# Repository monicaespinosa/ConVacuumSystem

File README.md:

# ConVacuumSystem
Later I will have time to explain what this is about. Let's start with the important things.

## Current circuit
The circuit (still to try) goes as following:

The setup still has to be simulated to find out V_c and to check the accuracy of the voltages selected for the grid and the plate.

## CST Simulations of the setup
The following setup was simulated:

Initially were the following voltages set:
* V_S 6.4 V
* V_C: 6.4 V
* V_G= 400 V
* V_P= 1000 V

The result for the obtained trajectory is shown below. The obtained current was around 5 mA.

However, the shape of the electron beams seems to change its shape in a very drastic way. Making the V_C smaller (more negative) should help concentring more the electrons to the center of the beam. A second simulation was made sweeping the voltage of the Wehnelt_Cylinider between -10 V and 6 V. 

As a result, the following charges on the plate were obtained:

Particles that come out of the coil:

They are only high when the voltage at the Wehnelt Cylinider is equal or higher than that of the coil. A new simulation sweeping Vc between 6.4V and 15.4V is been made. Results:

Evidently, the current (and as a consequence the particles getting to the plate) exists only when V_C>=V_S. The trajectories of the particles change however as they seem to be pushed into the cylinder (because of the higher voltage):

A new simulation setting the voltage on the grid V_G=800 V, putting a porcelain cylinder around the components (to simulate the glass cylinider) and moving the cylinider along the z-axis was made. The obtained trajectories are:

### Setting the voltage on the plate nearly to 0
Simulation with V_G = 1000 V and V_P = 4 V, and moving the cylinder to its initial position.

Simulation with the same parameters but moving the cylinder so its positioned closer to the plate.

Final simulation moving the cylinder back again and setting its voltage to -V_S.

### Variations of the voltage on the plate

Current incoming to the plate is the import_2 current.

Incoming particles:

### Changing the cathode
For all the following simulations the following voltages are set: V_S=6.4V, V_C=-30V V_G = 1000V and V_P = 4V.

#### Vertical filled PEC cylinder
Model:

Trajectories:

Total current leaving the cathode: 1.191e-03 mA

### Vertical hollow PEC cylinder
The cathode looks like the one before but is hollow with a thickness of 0.3 mm.

Trajectories:

Total current leaving the cathode: 9.14e-02 mA

### Toroid
Model:

Trajectories:

Total current leaving the cathode: 0.98 mA

### Rectangular cathode:
Model:

Trajectories: 

Total current leaving the cathode: 0.78 mA

### Sphere
Model:

Trajectories:

Total current leaving the cathode: 1.19 mA

### cut Cone:
Model:

It didn't emit any current when being put this way. However, when rotating like this:

The following trajectories are gotten:

Total current leaving the cathode: 0.71 mA

### Electron-gun Cathode
Model: 

It's a "cone" whose two planar circular faces are connected not by a rotated linear surface but a rotated exponential surface so it's internal radious get's thicker in an exponential way along the w axis as w decreases, simulating a pointy trunked cone. It was initially made small but only few particles were accelerated. Increasing its size and getting it closer to the grid produces the following trajectories:

The total current leaving the cathode was 9.35 mA. However the trajectories are messy and very disperse. After trying to move both the cathode and the grid further from the plate, because of the Wehnelt-Cylinder, the particles collide and then get dispersed again, without reaching the plate:

### Toroid-Coil

Model:

Trajectories: (actually a pretty straight beam)

However, the current incoming to the plate was not as high as expected. In this case, a variation of the voltage on the plate was made and the following curve obtained:

A dependency of the current to the voltage on the grid was also tested. The results below show in fact that the highest this voltage is, the highest the current.

As the shape of the beam seems to be well centered, another try using two toroids was given a shot. The model of the cathode goes as following:

As expected, the trajectories:

However the current across the platte is 50 uA. 

### Clapton Coil
This is the coil used normally for vapers. One of these was modelled in CST and looks like this:

The current incoming into the plate is 21.46uA. However, as the clapton coils that are found in the market have typically a diameter of 3.0mm, which for this project is too small. In order to increase the size of the cathode, a few of them can be placed together. For this purpose, four clapton coils forming a loop was simulated:

Trajectories: Not so straight directed to the center of the beam.

Current incoming to the plate: 0.18 mA

## Current measurement

### Methode
As mentioned before, this is the electrical structure of the setup:

The current measurement in between the plate and the voltage source V_p is more detailed here:

The current flowing through R_mess is theorically expected to be around 5mA according to the simulations. Supposing that the current is 10mA, the following circuit was simulated to choose the value of R_mess:

The voltage across Rm increases as Rm does. A value of Rm=140 ohm is temporarily chosen.

The following component is a amplifier that measures the voltage across the resistor R_mess and whose output is a digital signal whose amount of 1's is proportional to the current flowing through R_mess. The used amplifier is the Si8946A, that measures voltages between -62.5 mV and +62.5 mV, and whose output has a frequency of 10MHz. As this frequency is too high for a microcontroller like Arduino to read, a phase of signal conditioning is required. The simple RC filter produces an analog signal which corresponds to an average value of the quantity of 1's contained in the digital output of the amplifier. As this output is either a 0 or a 1, the analog response of the filter varies between 0V to 1V. However, as we intend to read this signal with Arduino, in order to take of advantage of all its measuring range the to-be-measured signal should be in the full range of 0V to 5V. This is the reason why an additional operational amplifier with a gain of 5 is used. The amplifier corresponds to the TLV9001 by Texas Instruments.

### PCB

The whole circuitry mentioned above, intended to be used for measuring the current caused by the electrons colliding into the plate and further flowing through R_mess, will be designed to be as close as posible to the plate. As not only the amount of current is important, but also the distribution of the electrons along the plate, this last is eventually going to be divided into many smaller plates whose incoming current will be measured separatedly. The first PCB designed to try the measuring circuitry has three plates. The PCB has two layers, one of them containing the plates

and the other one the Si8946A amplifiers and the connector in charge of providing feeding voltage and of letting the signals out. 

To know if the digital signal at 10 MHz is able to be carried by a normal jumper cable without using a SMA connector, some calculations need to be made:

Let's assume a square wave and use Bogatins rule of thumb [here](https://www.edn.com/rule-of-thumb-1-bandwidth-of-a-signal-from-its-rise-time/). According to the datasheet, the rise time is 20ns. The bandwidth of such a signal is 50 MHz, whose wavelength in free space is 6m, let's say 3m in the PCB. At 1/10th wavelength that's 30cm, which sets the upper limit to the jumper wire's length. 

Another option is to attach a second PCB using a PCB to PCB connector. 

>>>>>>> main

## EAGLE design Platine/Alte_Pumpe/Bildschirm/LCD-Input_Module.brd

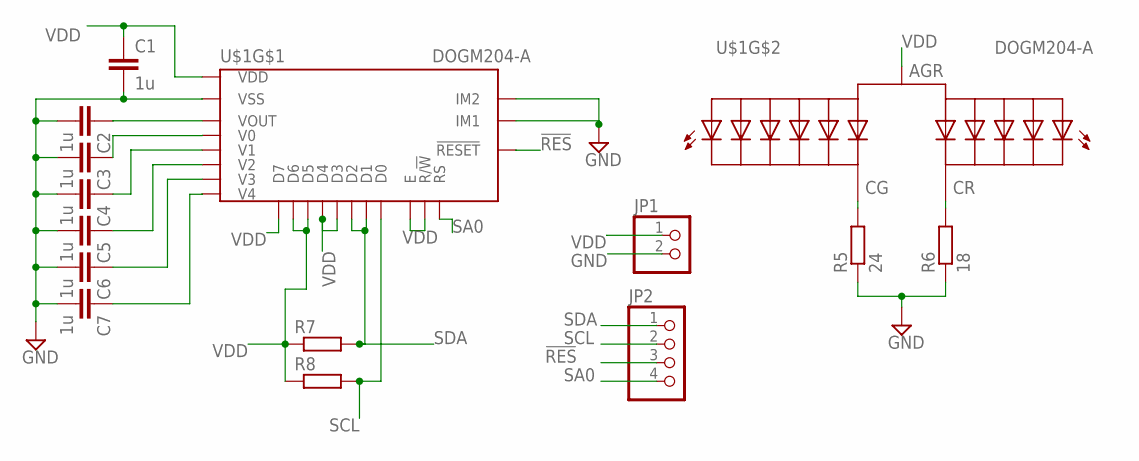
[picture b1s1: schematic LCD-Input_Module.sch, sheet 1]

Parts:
C1, C2, C3, C4, C5, C6, C7: 1u; C0603
JP1: PINHD-1X2; 1X02
JP2: PINHD-1X4; 1X04
R5: 24; R0603
R6: 18; R0603
R7, R8: R-EU_R0603; R0603
U$1: DOGM204-A; LCD

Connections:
!RES: JP2.3, U$1.P$44 (!RESET)
GND: C1.2, C2.2, C3.2, C4.2, C5.2, C6.2, C7.2, JP1.2, R5.1, R6.1, U$1.P$29 (IM2), U$1.P$30 (IM1), U$1.P$32 (VSS); also elsewhere on the board
unnamed: C3.1, U$1.P$24 (V0)
unnamed: C6.1, U$1.P$27 (V3)
unnamed: C4.1, U$1.P$25 (V1)
unnamed: C5.1, U$1.P$26 (V2)
unnamed: C7.1, U$1.P$28 (V4)
unnamed: C2.1, U$1.P$23 (VOUT)
unnamed: R5.2, U$1.P$21 (CG)
unnamed: R6.2, U$1.P$22 (CR)
SA0: JP2.4, U$1.P$43 (RS)
SCL: JP2.2, R8.2, U$1.P$40 (D0)
SDA: JP2.1, R7.2, U$1.P$38 (D2), U$1.P$39 (D1)
VDD: C1.1, JP1.1, R7.1, R8.1, U$1.P$1 (AGR), U$1.P$31 (VDD), U$1.P$33 (D7), U$1.P$34 (D6), U$1.P$35 (D5), U$1.P$36 (D4), U$1.P$37 (D3), U$1.P$41 (E), U$1.P$42 (R/!W); also elsewhere on the board

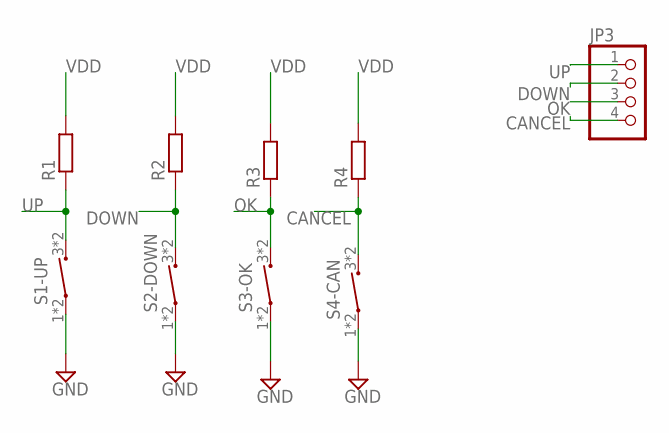
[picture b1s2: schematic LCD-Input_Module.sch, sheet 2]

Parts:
JP3: PINHD-1X4; 1X04
R1, R2, R3, R4: R-EU_R0603; R0603
S1-UP, S2-DOWN, S3-OK, S4-CAN: PTS647; PTS647-TACTSWITCH

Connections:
CANCEL: JP3.4, R4.1, S4-CAN.3 (2), S4-CAN.4 (2)
DOWN: JP3.2, R2.1, S2-DOWN.3 (2), S2-DOWN.4 (2)
GND: S1-UP.1, S1-UP.2 (1), S2-DOWN.1, S2-DOWN.2 (1), S3-OK.1, S3-OK.2 (1), S4-CAN.1, S4-CAN.2 (1); also elsewhere on the board
OK: JP3.3, R3.1, S3-OK.3 (2), S3-OK.4 (2)
UP: JP3.1, R1.1, S1-UP.3 (2), S1-UP.4 (2)
VDD: R1.2, R2.2, R3.2, R4.2; also elsewhere on the board

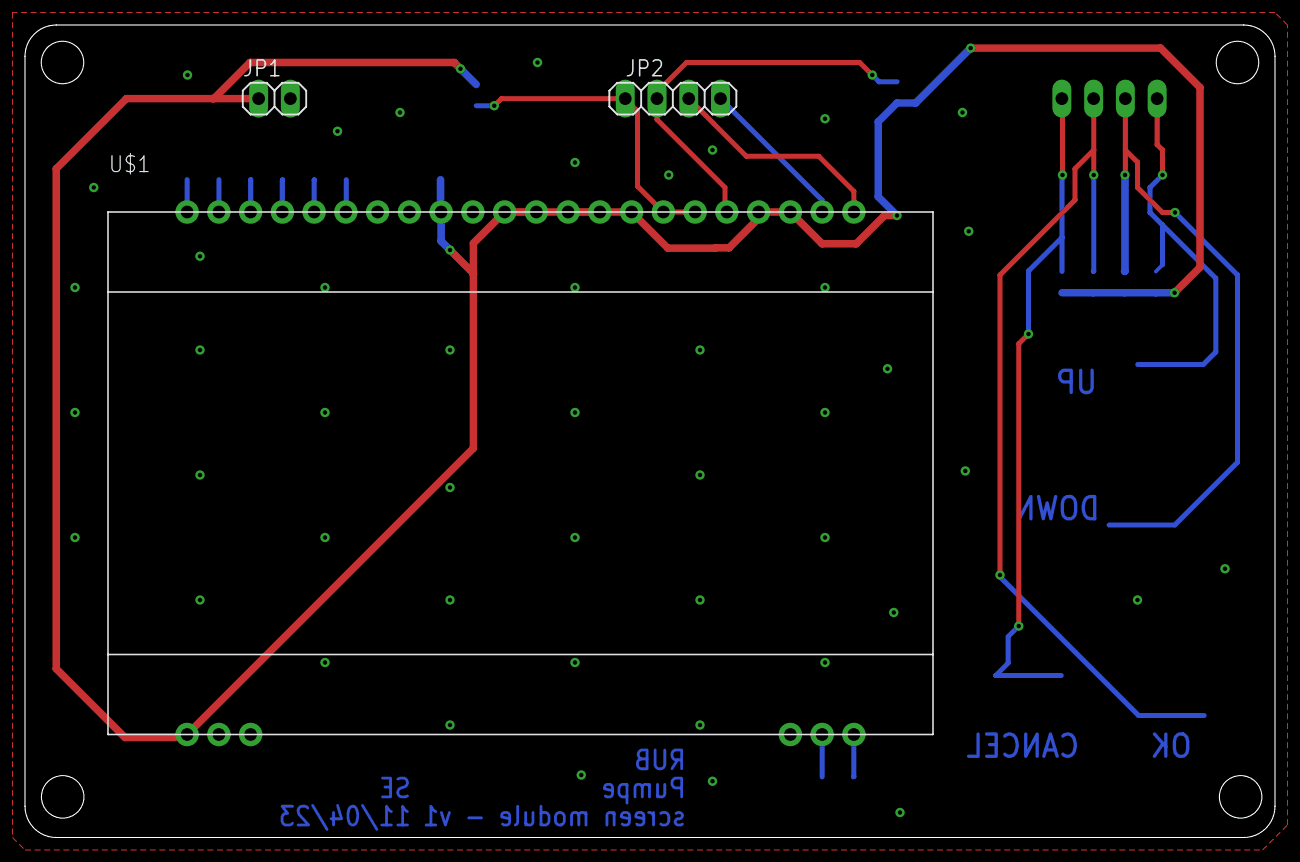
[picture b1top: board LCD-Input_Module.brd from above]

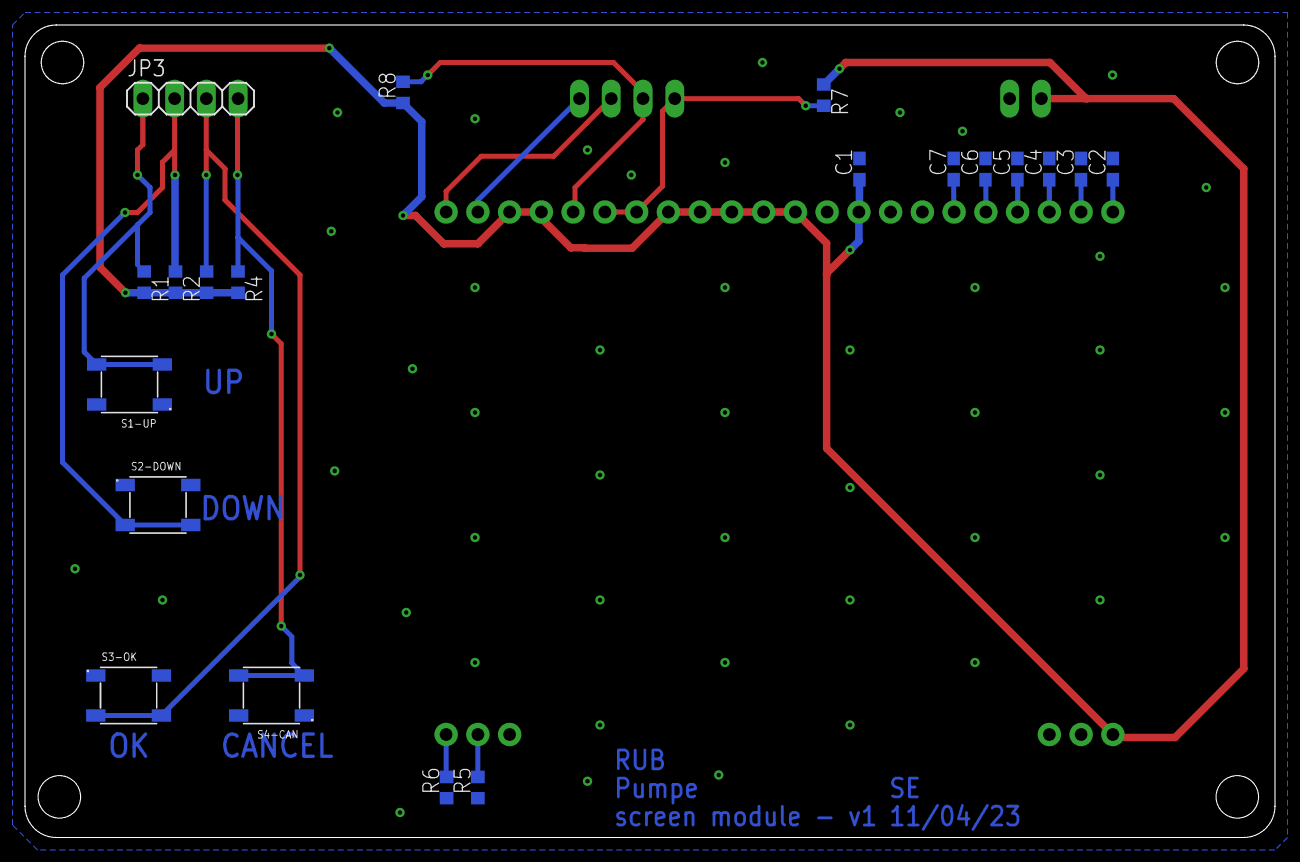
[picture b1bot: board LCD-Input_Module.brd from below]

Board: 2 copper layers, 100.0 x 65.0 mm, 23 parts (20 on the bottom side), 18 nets.

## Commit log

2023-12-28 Create README.md
    general description of the arduino program.
    For now, the program is not divided into libraries and it will be uploaded in function parts and UI parts.
2023-12-28 Create PumpComm_SensorRead.ino
    General program of the functionality of the control unit. Here it is a block of code, the idea is to separate it into libraries.
2024-01-15 Create PumpScreenUI.ino
    First functions of the screen UI. This is a display of the data acquire from the pump comm and the sensor.
2024-01-15 Changing screen arduino code so it works with the board
2024-01-29 Interruption code started
    Initial interruption code, more tests need to be done
2024-02-05 Interruption code tested. It works.
2024-02-16 Create the library for the pressure sensor ITR090 - RS232Comm protocol
2024-02-19 Nothing
2024-02-26 Changes on screen code
2024-02-26 Ergänzung der Projekte der Platinen.
2024-02-26 Small change in schematic
2024-02-26 Interruption Test code changed, it works
2024-03-04 State Maschine Programmierung v.1
2024-03-04 Testing selecting arrow part 1
2024-03-04 Other tests with the screen code
2024-03-04 Screen code ready (for now)
2024-03-06 DCU library / turbo pump library done. requires testing. compiles without errors or warnings
2024-03-07 Test function for the arrown added to the LCD code
2024-03-08 turbopump library tested and corrected. works until this point, maybe further changes
2024-03-08 Delete Arduino/PumpComm_SensorRead directory
    to allow commit
2024-03-11 Merging screen code with control code
2024-03-11 Screen code merged with main code. Still missing to adjust some function imput variables
2024-03-15 Relevant datasheets and documents for the vacuum setup
2024-03-15 Additional info for working with turbopumps
2024-03-15 Code completely merged
2024-03-20 Some changes to the screen code
2024-03-25 Adding comments to sensor ITR 90 library
2024-03-25 same as before
2024-03-25 Code fixed so it reads correctly the ITR90 sensor
2024-03-26 adding function to turn on/off the pumps through the lcd screen
2024-04-08 starting virtual screen with python
2024-04-21 Changes to python code
2024-04-22 nthng
2024-04-22 Finished screens in python, now arranging char array from arduino to python
2024-04-23 some changes
2024-04-23 python code almost ready
2024-04-24 the code works
2024-06-18 added command to indicate the ITR090 sensor that the pressure units are mbar
2024-06-21 Added Draft2.asc
2024-08-23 RunningMoreSims.md
2024-09-04 EndOfSimulations.md
2024-09-11 Viel hat geändert
2024-09-11 virtualler Bildschirm changes
2024-09-13 Nichts
2024-09-18 Adding a CST simulation
2024-09-18 Adding CST simulation with filled cylinder
2024-09-18 Adding Hohlzylinider CST simulation
2024-09-20 Uploading PCB of the current measuring plate
2024-09-23 Changes to plate PCB
2024-09-23 Plate PCB almost done
2024-09-25 Few changes plate PCB
2024-09-25 small changes
2024-09-25 Adding now RC filter and DC Converter to Plate PCB
2024-09-30 Nothing special
2024-10-01 adding signal conditioning phase to plate PCB
2024-10-02 not much
2024-10-03 Results of changing the voltage on the plate on README file
2024-10-03 plate pcb almost finished
2024-10-04 Removing CST simulations because of weight, theyre now in the folder outside the repo
2024-10-07 Adding footprints to signal conditioning PCB and placing components
2024-10-08 PCBs almost finished
2024-10-09 PCBs completely finished
2024-10-09 Mit Robin geredet, ein paar Veränderung gemacht
2024-10-10 LTSpice sim
2024-10-21 LTSpice simulation almost done
2024-10-21 4 clapton coils simulation result.md
2024-10-21 LTSpice simulation done. Changing now schematics and PCB
2024-10-21 nicht so viel
2024-10-23 PCBs ready
2024-10-23 Modifying working frequency in LTSpice and adding extra resistor in pcb
2024-10-24 mit Robin geredet
2024-10-25 Simulation verändert und fertiggemacht
2024-10-29 Final circuits designed. Plate PCB ready, signal cond PCB still in process
2024-10-30 Made a few changes to PCBs and schematics
2024-10-30 Both the PCBs finished
2024-10-31 Small correction. Everything finished
2024-11-05 Better shaping the Plates on the PCB
2024-11-13 Ein paar Änderungen
2025-01-31 All the changes until today
2025-02-06 Updated Arduino code for reading test PCB
2025-02-11 Changes in LTSpice simulations
2025-02-11 corrections on platte PCB
2025-02-11 trying to merge
2025-02-12 Starting with final PCB
2025-02-13 changes in new pcb
2025-02-16 a lot of advance in final PCB
2025-02-18 still need to finish routing
2025-02-18 Almost done with routing
2025-02-19 final PCB finished
2025-02-19 Added grid voltage connector
2025-02-20 Commit before changing PCB connectors, just in case
2025-02-20 Changed connectors according to stock. Added auxiliar projects for printing each PCB, added component list
2025-02-20 bom_list file from kicad added
2025-02-24 adding some matlab simulations and graphs
2025-02-24 trying to merge again
2025-02-28 just committing local changes
2025-02-28 added 3D milling part
2025-03-03 ard code updated
2025-03-09 no idea
2025-03-10 updated Arduino code
2025-03-11 small changes on Arduino code
2025-03-11 added python code for visualizing currents
2025-03-12 made ard code for 1 surface anode
2025-03-12 added capture of measurement
2025-03-20 Vortrag Vorlage
